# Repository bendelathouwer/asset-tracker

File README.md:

# LoRa asset tracker
a Lora asset tracker loosly based on a arduino mkr wan 1310. This asset tracker is going to be used on the quadVelo. 
And is made with the eurocircuits tool and for eurocircuits

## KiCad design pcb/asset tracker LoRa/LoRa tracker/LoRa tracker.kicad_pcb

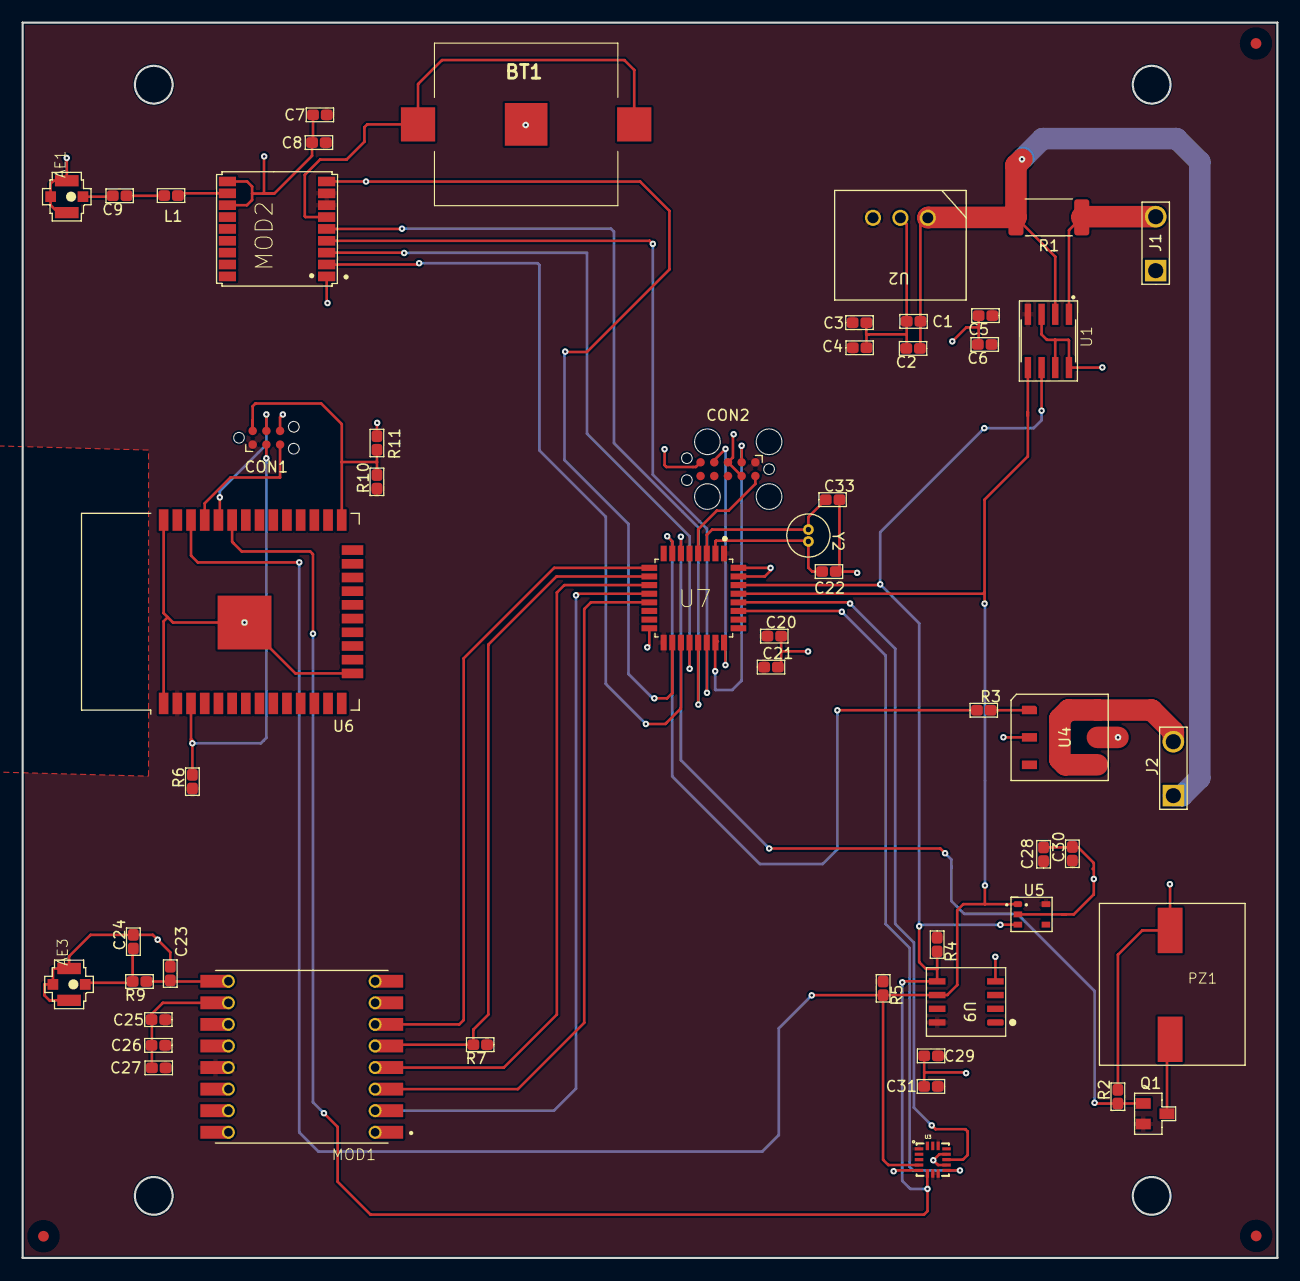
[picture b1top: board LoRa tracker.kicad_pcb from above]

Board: 2 copper layers, 116.3 x 114.5 mm, 53 parts (0 on the bottom side), 38 nets.

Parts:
AE1: sma; ufl connector
AE3: Antenna_Shield; ufl connector
BT1: Battery_Cell; 3012TR
C1, C3, C6, C8, C20, C28, C30: 100nF; 0603
C2, C4, C5, C7, C25, C29, C31: 10uF; 0603
C9: 120nF; 0603
C21, C26: 1uF; 0603
C22, C33: 6.8pF; 0603
C23, C24: NM; 0603
C27: 0.1uF; 0603
CON1: TAGconnect_ESP; Tag-Connect_TC2030-IDC-NL_2x03_P1.27mm_Vertical
CON2: jtag; Tag-Connect_TC2050-IDC-FP_2x05_P1.27mm_Vertical
J1, J2: Screw_Terminal_01x02; 2pin_screw
L1: 5n6; 0603
MOD1: RFM98W-433S2; XCVR_RFM98W-433S2
MOD2: teseo-LIV; SON_STM_TESEO-LIV3R
PZ1: buzzer; PROSIGNAL_ABI-017-RC
Q1: BSS138; sot-23,
R1: 100m Ohm; R_2512_6332Metric_Pad1.40x3.35mm_HandSolder
R2, R4, R5: 10K; 0603
R3: 220; 0603
R6, R7, R10: 10K; 0603RL
R9: 0; 0603RL
R11: NM; 0603RL
U1: INA219BxDCN; SOIC127P599X175-8N
U2: R-783.3-1.0; recom psu
U3: LIS3DH; QFN-16_0.5MM
U4: G3VM-61HR2(TR05); sop4 P=2.54
U5: DS28CM00R-A00+T; SOT-25
U6: ESP32-WROOM; ESP32-WROOM-32
U7: STM32L052K6Tx; QFP32P80_900X900X160L60X37N
U9: ATECC608B; soic p1.27 lengt 5.40
Y2: 32khz; crystal tht

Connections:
+3V3: C3.1, C4.1, C5.1, C6.1, C7.1, C8.1, C20.1, C21.1, C25.1, C26.1, C27.1, C28.1, C29.1, C30.1, C31.1, CON1.1 (VCC), CON2.1 (VCC), MOD1.13 (3.3V), MOD1.13_1 (3.3V), MOD2.7 (VCC_IO), MOD2.8 (VCC), Q1.2, R4.1, R5.1, R6.1, R7.1, R10.1, U1.4 (VS), U2.3 (OUT), U3.1 (VDD_IO), U3.7 (SDO/SA0), U3.8 (CS), U3.14 (VDD), U5.5 (VCC), U6.2 (3V3), U7.1 (VDD), U7.5 (VDDA), U7.17 (VDD), U9.8 (VCC)
/BUZZER: Q1.1, R2.1, U7.6 (PA0)
/CS: MOD1.5 (NSS), MOD1.5_1 (NSS), R7.2, U7.10 (PA4)
/INT1: U3.11 (INT1), U7.28 (PB5)
/INT2: U3.9 (INT2), U7.27 (PB4)
/LoRa_RFM/ANT: C23.1, MOD1.9 (ANT), MOD1.9_1 (ANT), R9.1
/MISO: MOD1.2 (MISO), MOD1.2_1 (MISO), U7.12 (PA6)
/MOSI: MOD1.3 (MOSI), MOD1.3_1 (MOSI), U7.13 (PA7)
/PPS: MOD2.4 (PPS), U7.22 (PA12)
/RESET: MOD1.6 (RESET), MOD1.6_1 (RESET), U7.9 (PA3)
/RESET_GPS: MOD2.9 (SYS_RESET), U7.18 (PA8)
/RX: MOD2.3 (RX), U7.20 (PA10)
/SCK: MOD1.4 (SCK), MOD1.4_1 (SCK), U7.11 (PA5)
/SCL: R5.2, U1.5 (SCL), U3.4 (SCL/SPC), U5.1 (SCL), U6.36 (IO22), U7.29 (PB6), U9.6 (SCL)
/SDA: R4.2, U1.6 (SDA), U3.6 (SDA/SDI/SDO), U5.3 (SDA), U6.33 (IO21), U7.30 (PB7), U9.5 (SDA)
/SSR: R3.1, U7.7 (PA1)
/TX: MOD2.2 (TX), U7.19 (PA9)
/WAKE: MOD2.5 (WAKE), U7.21 (PA11)
/esp32/GPIO0: CON1.2 (GPIO0), R10.2, R11.1, U6.25 (IO0)
/esp32/RESET: CON1.3 (RESET), R6.2, U6.3 (EN)
/esp32/RX: CON1.4 (RX), U6.34 (RXD0)
/esp32/TX: CON1.5 (TX), U6.35 (TXD0)
/mcu/OSC_32_IN: C22.1, U7.2 (PC14), Y2.2
/mcu/OSC_32_OUT: C33.1, U7.3 (PC15), Y2.1
/mcu/RST: CON2.10 (tRST), U7.4 (NRST)
/mcu/SWDCLK: CON2.4 (SWDCLK/TCK), U7.24 (PA14)
/mcu/SWDIO: CON2.2 (SWDIO/TMS), U7.23 (PA13)
GND: AE1.2 (Shield), AE3.2 (Shield), BT1.2 (-), C1.2, C2.2, C3.2, C4.2, C5.2, C6.2, C7.2, C8.2, C20.2, C21.2, C22.2, C23.2, C24.2, C25.2, C26.2, C27.2, C28.2, C29.2, C30.2, C31.2, C33.2, CON1.6 (GND), CON2.3 (GND), CON2.5 (GND), CON2.9 (GND), J1.1, MOD1.1 (GND), MOD1.1_1 (GND), MOD1.8 (GND), MOD1.8_1 (GND), MOD1.10 (GND), MOD1.10_1 (GND), MOD2.1 (GND), MOD2.10 (GND_RF), MOD2.12 (GND_RF), PZ1.2, R2.2, R11.2, U1.3 (GND), U1.7 (A0), U1.8 (A1), U2.2 (GND), U3.5 (GND), U3.10 (GND), U3.12 (GND), U4.2 (Catode), U4.5 (OUT2), U5.2 (GND), U6.1 (GND), U6.15 (GND), U6.38 (GND), U6.39 (GND-PAD), U7.16 (VSS), U7.31 (BOOT0), U7.32 (VSS), U9.4 (GND)
unnamed: AE1.1 (A), C9.2
unnamed: AE3.1 (A), C24.1, R9.2
unnamed: BT1.1 (+), MOD2.6 (VBAT)
unnamed: C9.1, L1.2
unnamed: J1.2, R1.1, U1.1 (IN+)
unnamed: J2.2, U4.4 (OUT1), U4.6 (OUT3)
unnamed: L1.1, MOD2.11 (RF_IN)
unnamed: PZ1.1, Q1.3
unnamed: R3.2, U4.1 (Anode)
VDC: C1.1, C2.1, J2.1, R1.2, U1.2 (IN-), U2.1 (IN)

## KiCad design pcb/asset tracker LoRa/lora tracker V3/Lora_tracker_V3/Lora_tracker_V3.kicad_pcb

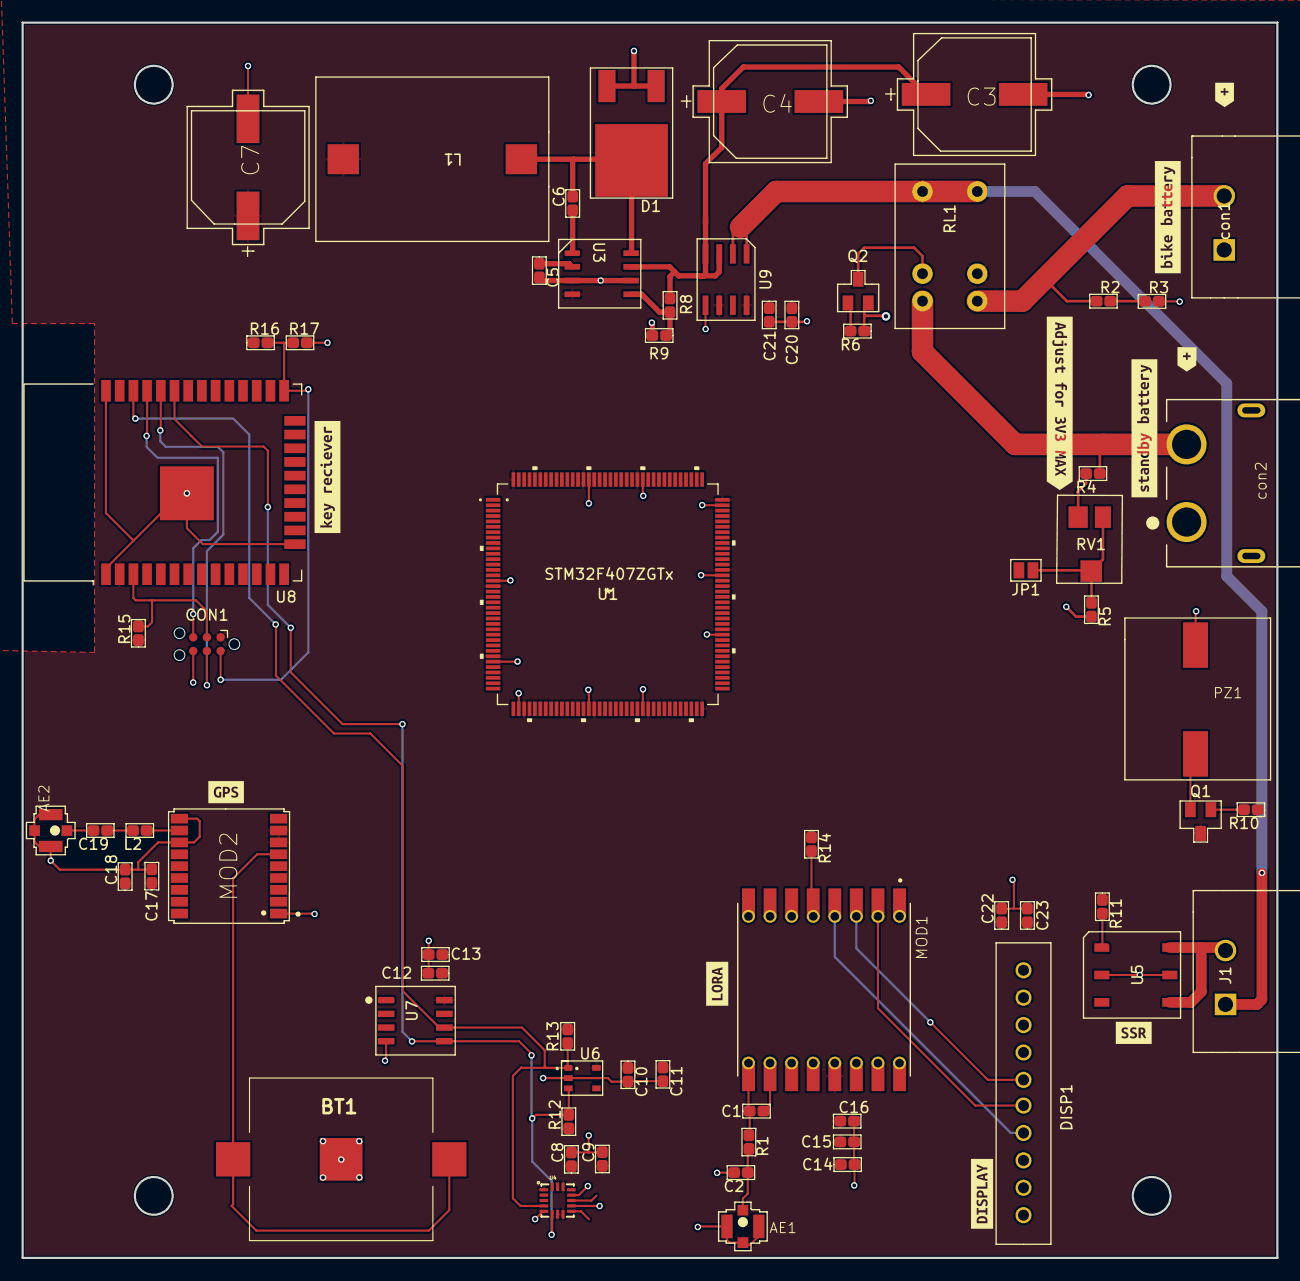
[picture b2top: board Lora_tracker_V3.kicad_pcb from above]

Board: 2 copper layers, 116.3 x 114.5 mm, 76 parts (0 on the bottom side), 36 nets.

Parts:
AE1: Antenna_Shield; ufl connector
AE2: sma; ufl connector
BT1: Battery_Cell; 3012TR
C1, C2: NM; 0603
C3: 68uF/100V; CAPAE1030X1050D1200L350X90N
C4: 0.22uF/100V; CAPAE1030X1050D1200L350X90N
C5, C6, C16: 0.1uF; 0603
C7: 68uF/10V; CAPAE1030X1050D1200L350X90N
C8, C11, C13, C14, C17, C20, C22: 10uF; 0603
C9, C10, C12, C18, C23: 100nF; 0603
C15: 1uF; 0603
C19: 120nF; 0603
C21: 10nF; 0603
CON1: TAGconnect_ESP; Tag-Connect_TC2030-IDC-NL_2x03_P1.27mm_Vertical
D1: MBRM5100; DPAK
DISP1: ConnectEVE; 10pin header
J1: Screw_Terminal_01x02; 2pin_screw
JP1: Jumper_2_Open; SolderJumper-2_P1.3mm_Open_Pad1.0x1.5mm
L1: 100uH; DO5022p
L2: 5n6; 0603
MOD1: RFM98W-433S2; XCVR_RFM98W-433S2
MOD2: teseo-LIV; SON_STM_TESEO-LIV3R
PZ1: buzzer; PROSIGNAL_ABI-017-RC
Q1, Q2: BSS138; sot-23,
R1: 0; 0603RL
R2: 1Mohm; 0603
R3: 58Kohm; 0603
R4: 900K; 0603
R5: 58K; 0603
R6, R10, R12, R13: 10K; 0603
R8: 43.5Kohm/1%; 0603
R9: 130Kohm/1%; 0603
R11: 220; 0603
R14, R15, R16: 10K; 0603RL
R17: NM; 0603RL
RL1: Relais; G5V-1
RV1: 100K; 3314G-1-201E bourns trimmer
U1: STM32F407ZGTx; STM32F407ZGT6
U3: MAX5035AUSA; soic HV clearance
U4: LIS3DH; QFN-16_0.5MM
U5: G3VM-61HR2(TR05); sop4 P=2.54
U6: DS28CM00R-A00+T; SOT-25
U7: ATECC608B; soic p1.27 lengt 5.40
U8: ESP32-WROOM; ESP32-WROOM-32
U9: MLX91221; SOIC-8
con1: screw terminal; 2pin_screw
con2: xt60; AMASS_XT60PW-F
kibuzzard-613B3452: G***; kibuzzard-613B3452
kibuzzard-613B3465: G***; kibuzzard-613B3465
kibuzzard-613B6735: G***; kibuzzard-613B6735
kibuzzard-613B6746: G***; kibuzzard-613B6746
kibuzzard-613B6752: G***; kibuzzard-613B6752
kibuzzard-613F18F5: G***; kibuzzard-613F18F5
kibuzzard-613F1907: G***; kibuzzard-613F1907
kibuzzard-61389C09, kibuzzard-61389C09#2: G***; kibuzzard-61389C09
kibuzzard-61389CC5: G***; kibuzzard-61389CC5

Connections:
+3V3: C7.1, C8.1, C9.1, C10.1, C11.1, C12.1, C13.1, C14.1, C15.1, C16.1, C17.1, C18.1, C20.1, C21.1, C22.1, C23.1, CON1.1 (VCC), DISP1.9 (VCC_3V3), L1.2, MOD1.13 (3.3V), MOD1.13_1 (3.3V), MOD2.7 (VCC_IO), MOD2.8 (VCC), Q1.3 (D), R10.1, R12.1, R13.1, R14.1, R15.1, R16.1, RL1.2, U1.17 (VDD), U1.30 (VDD), U1.33 (VDDA), U1.39 (VDD), U1.52 (VDD), U1.62 (VDD), U1.72 (VDD), U1.84 (VDD), U1.95 (VDD), U1.108 (VDD), U1.121 (VDD), U1.131 (VDD), U1.144 (VDD), U3.4 (FB), U4.1 (VDD_IO), U4.7 (SDO/SA0), U4.8 (CS), U4.14 (VDD), U6.5 (VCC), U7.8 (VCC), U8.2 (3V3), U9.6 (VREF), U9.8 (VDD)
/BUZZER: Q1.1 (G), R10.2
/CLK: DISP1.4 (SCK), MOD1.4 (SCK), MOD1.4_1 (SCK)
/CS: MOD1.5 (NSS), MOD1.5_1 (NSS), R14.2
/Lora_RFM/ANT: C1.1, MOD1.9 (ANT), MOD1.9_1 (ANT), R1.1
/MISO: DISP1.5 (MISO), MOD1.2 (MISO), MOD1.2_1 (MISO)
/MOSI: DISP1.6 (MOSI), MOD1.3 (MOSI), MOD1.3_1 (MOSI)
/RELAY: Q2.1 (G), R6.2
/RESET_LORA: MOD1.6 (RESET), MOD1.6_1 (RESET)
/SCL: R13.2, U4.4 (SCL/SPC), U6.1 (SCL), U7.6 (SCL), U8.36 (IO22)
/SDA: R12.2, U4.6 (SDA/SDI/SDO), U6.3 (SDA), U7.5 (SDA), U8.33 (IO21)
/Voltage1: R2.2, R3.1
/esp32/GPIO0: CON1.2 (GPIO0), R16.2, R17.1, U8.25 (IO0)
/esp32/RESET: CON1.3 (RESET), R15.2, U8.3 (EN)
/esp32/RX: CON1.4 (RX), U8.34 (RXD0)
/esp32/TX: CON1.5 (TX), U8.35 (TXD0)
/voeding/DC_DC/VIN DC_DC: C3.1, C4.1, R8.1, U3.7 (VIN), U9.3 (IP-), U9.4 (IP-)
GND: AE1.2 (Shield), AE2.2 (Shield), BT1.2 (-), C1.2, C2.2, C3.2, C4.2, C5.2, C7.2, C8.2, C9.2, C10.2, C11.2, C12.2, C13.2, C14.2, C15.2, C16.2, C17.2, C18.2, C20.2, C21.2, C22.2, C23.2, CON1.6 (GND), D1.1, D1.3, DISP1.10 (GND), MOD1.1 (GND), MOD1.1_1 (GND), MOD1.8 (GND), MOD1.8_1 (GND), MOD1.10 (GND), MOD1.10_1 (GND), MOD2.1 (GND), MOD2.10 (GND_RF), MOD2.12 (GND_RF), PZ1.2, Q2.2 (S), R3.2, R5.2, R6.1, R9.2, R17.2, U1.16 (VSS), U1.31 (VSSA), U1.38 (VSS), U1.51 (VSS), U1.61 (VSS), U1.83 (VSS), U1.94 (VSS), U1.107 (VSS), U1.120 (VSS), U1.130 (VSS), U3.3 (SGND), U3.6 (GND), U4.5 (GND), U4.10 (GND), U4.12 (GND), U5.2 (Catode), U5.5 (OUT2), U6.2 (GND), U7.4 (GND), U8.1 (GND), U8.15 (GND), U8.38 (GND), U8.39 (GND-PAD), U9.5 (GND), con1.1 (-), con2.1 (-)
unnamed: AE1.1 (A), C2.1, R1.2
unnamed: AE2.1 (A), C19.2
unnamed: BT1.1 (+), MOD2.6 (VBAT)
unnamed: C5.1, U3.2 (VD)
unnamed: C6.1, U3.1 (BST)
unnamed: C6.2, D1.4, L1.1, U3.8 (LX)
unnamed: C19.1, L2.2
unnamed: J1.2, U5.4 (OUT1), U5.6 (OUT3)
unnamed: JP1.1 (A), R5.1, RV1.2, RV1.3
unnamed: L2.1, MOD2.11 (RF_IN)
unnamed: PZ1.1, Q1.2 (S)
unnamed: Q2.3 (D), RL1.1
unnamed: R2.1, RL1.5, con1.2 (+)
unnamed: R4.1, RL1.4, con2.2 (+)
unnamed: R4.2, RV1.1
unnamed: R8.2, R9.1, U3.5 (ON/~OFF)
unnamed: R11.2, U5.1 (Anode)
VDC: J1.1, RL1.3, U9.1 (IP+), U9.2 (IP+)

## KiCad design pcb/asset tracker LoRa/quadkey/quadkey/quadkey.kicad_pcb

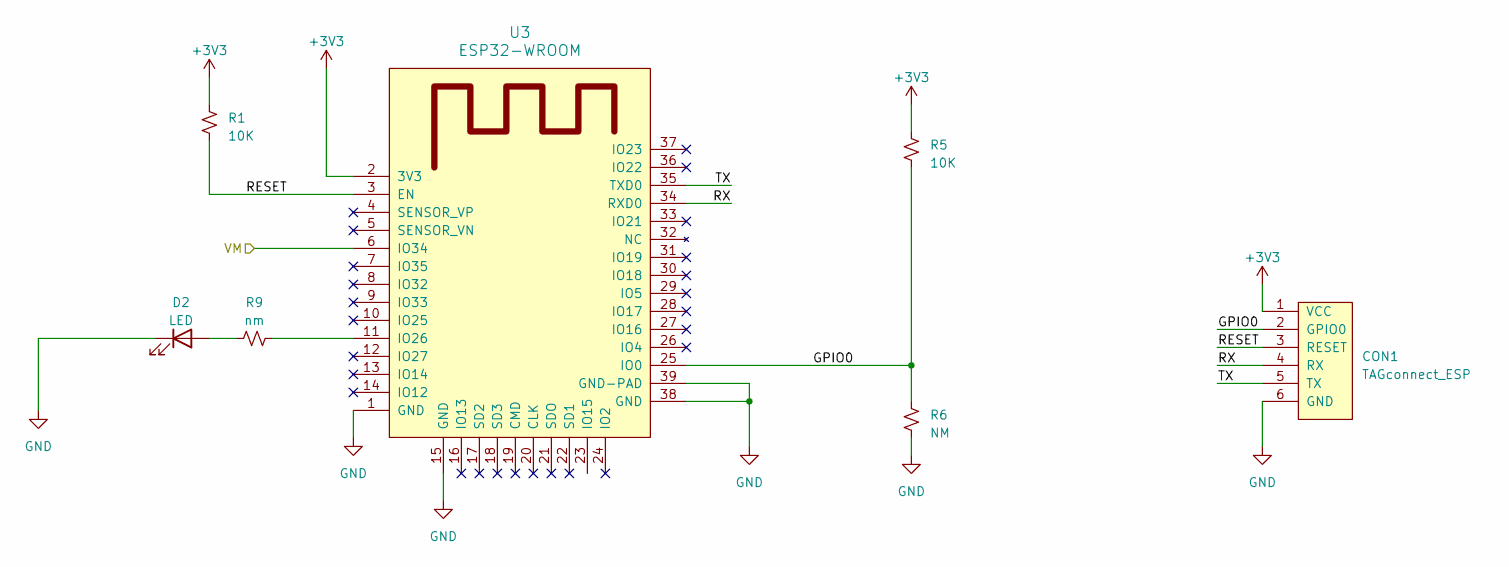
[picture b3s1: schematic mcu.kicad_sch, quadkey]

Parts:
CON1: TAGconnect_ESP; Tag-Connect_TC2030-IDC-NL_2x03_P1.27mm_Vertical
D2: LED; led0603
R1, R5: 10K; 0603RL
R6: NM; 0603RL
R9: nm; 0603RL
U3: ESP32-WROOM; ESP32-WROOM-32

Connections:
+3V3: CON1.1 (VCC), R1.1, R5.1, U3.2 (3V3); also elsewhere on the board
/mcu/GPIO0: CON1.2 (GPIO0), R5.2, R6.1, U3.25 (IO0)
/mcu/RESET: CON1.3 (RESET), R1.2, U3.3 (EN)
/mcu/RX: CON1.4 (RX), U3.34 (RXD0)
/mcu/TX: CON1.5 (TX), U3.35 (TXD0)
/mcu/VM: U3.6 (IO34); also elsewhere on the board
GND: CON1.6 (GND), D2.1 (K), R6.2, U3.1 (GND), U3.15 (GND), U3.38 (GND), U3.39 (GND-PAD); also elsewhere on the board
unnamed: D2.2 (A), R9.1
unnamed: R9.2, U3.11 (IO26)

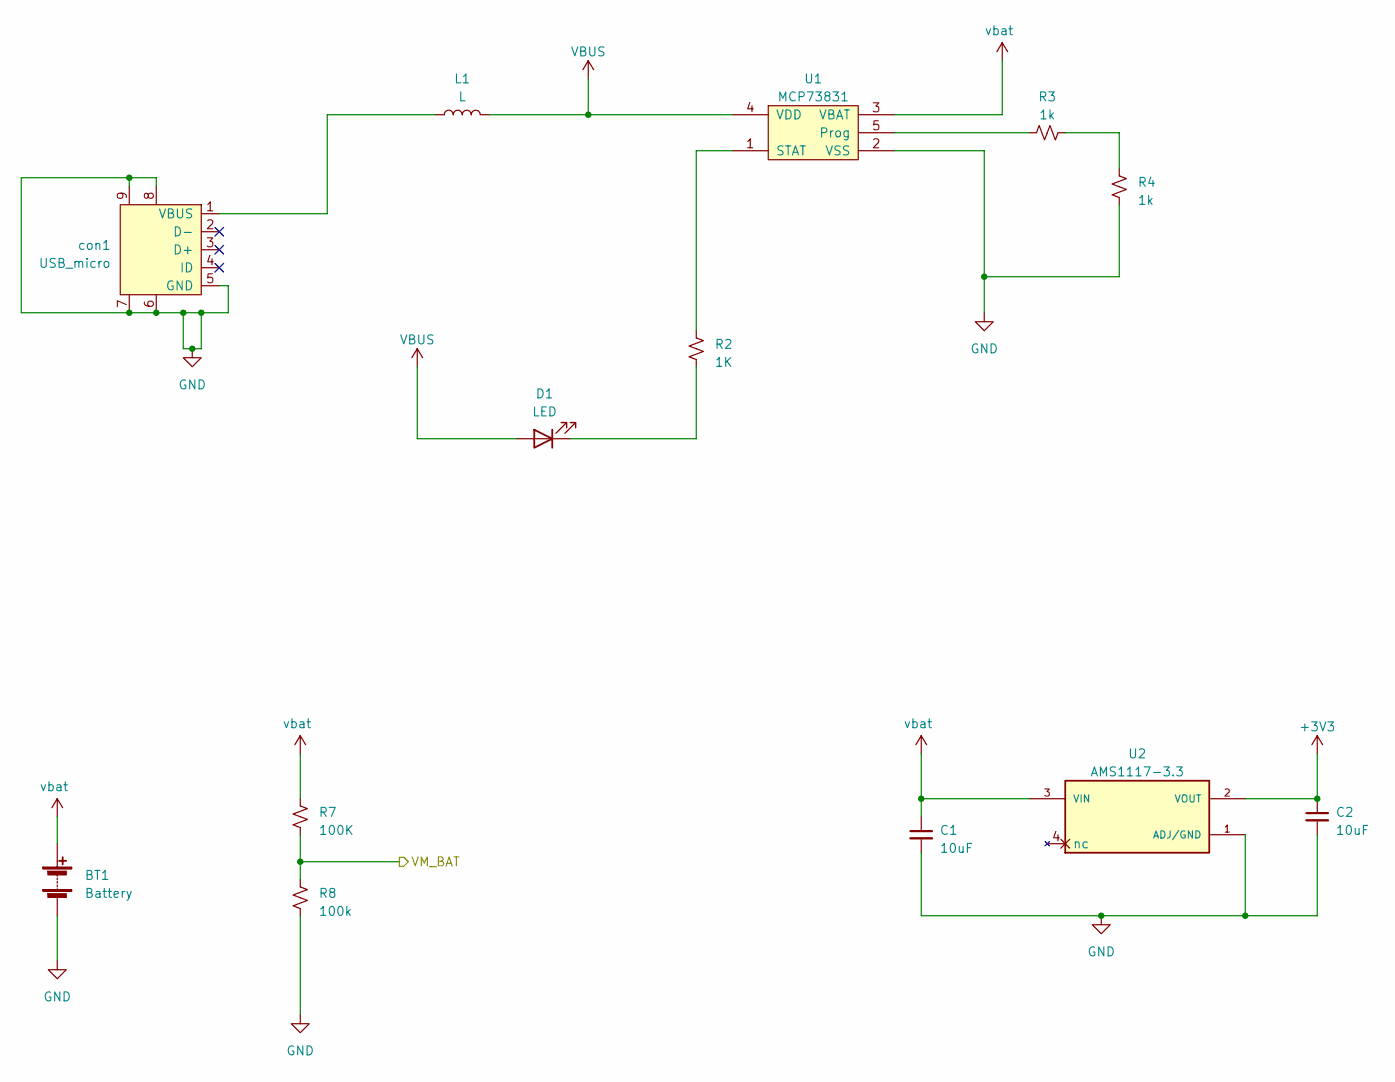
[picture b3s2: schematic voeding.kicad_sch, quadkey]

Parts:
BT1: Battery; jst 2 pin
C1, C2: 10uF; 0603
D1: LED; led0603
L1: L; 0603RL
R2: 1K; 0603RL
R3, R4: 1k; 0603RL
R7: 100K; 0603RL
R8: 100k; 0603RL
U1: MCP73831; SOT-25
U2: AMS1117-3.3; SOT229P700X180-4N; PARTREV NA
con1: USB_micro; MILLMAX_897-43-005-00-100001

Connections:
+3V3: C2.1, U2.2 (VOUT); also elsewhere on the board
/mcu/VM: R7.1, R8.2; also elsewhere on the board
GND: BT1.2 (-), C1.2, C2.2, R4.1, R8.1, U1.2 (VSS), U2.1 (ADJ/GND), con1.5 (GND), con1.6, con1.7, con1.8, con1.9; also elsewhere on the board
unnamed: D1.1 (K), R2.2
unnamed: L1.1, con1.1 (VBUS)
unnamed: R2.1, U1.1 (STAT)
unnamed: R3.1, U1.5 (Prog)
unnamed: R3.2, R4.2
VBAT: BT1.1 (+), C1.1, R7.2, U1.3 (VBAT), U2.3 (VIN)
VBUS: D1.2 (A), L1.2, U1.4 (VDD)

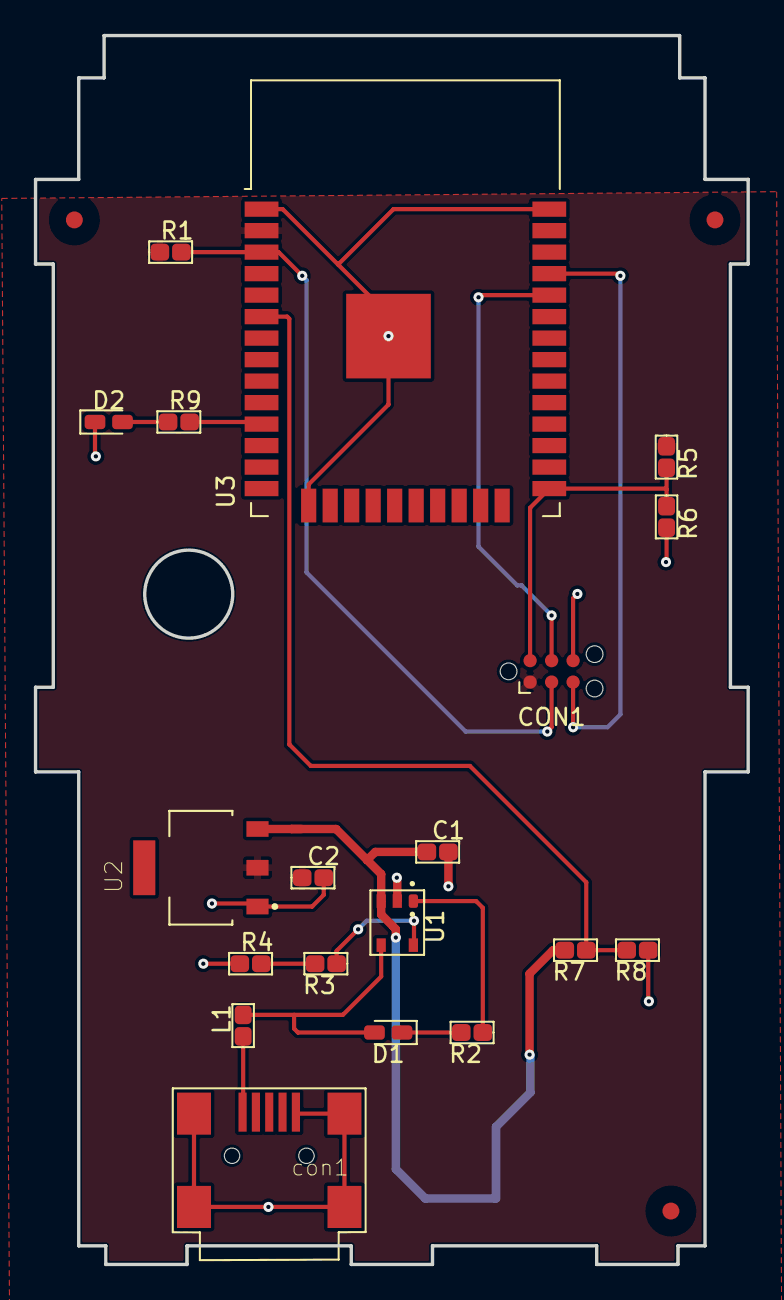
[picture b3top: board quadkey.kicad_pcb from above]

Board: 2 copper layers, 42.1 x 72.6 mm, 20 parts (1 on the bottom side), 16 nets.

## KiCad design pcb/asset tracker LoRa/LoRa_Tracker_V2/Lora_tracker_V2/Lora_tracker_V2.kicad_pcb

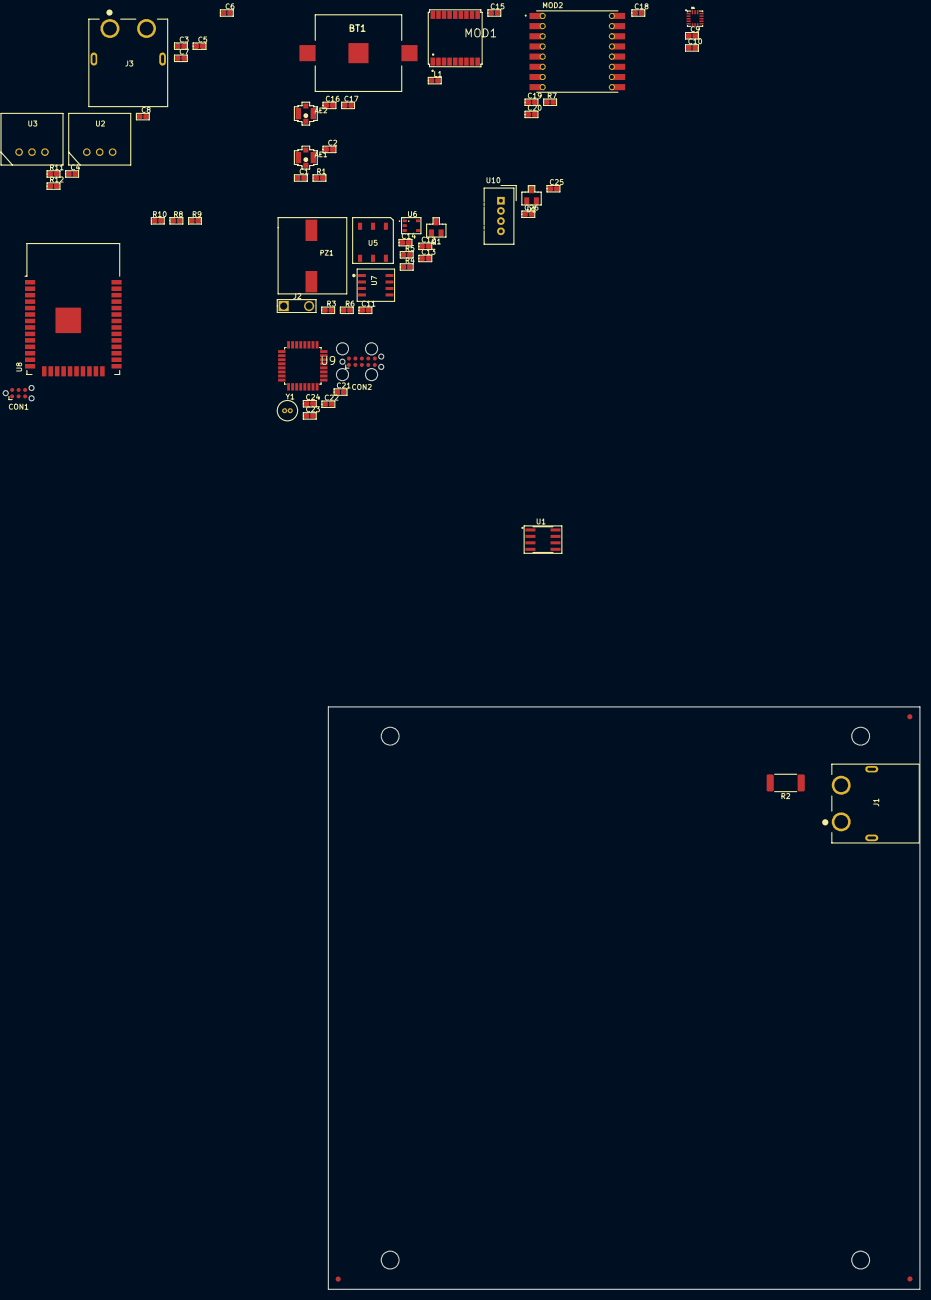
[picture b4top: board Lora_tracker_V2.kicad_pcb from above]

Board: 2 copper layers, 116.3 x 114.5 mm, 63 parts (0 on the bottom side), 44 nets, no tracks yet.

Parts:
AE1: Antenna_Shield; ufl connector
AE2: sma; ufl connector
BT1: Battery_Cell; 3012TR
C1, C2: NM; 0603
C3, C5, C7, C10, C11, C13, C16, C21, C25: 100nF; 0603
C4, C6, C8, C9, C12, C14, C15, C18, C26: 10uF; 0603
C17: 120nF; 0603
C19, C22: 1uF; 0603
C20: 0.1uF; 0603
C23, C24: 6.8pF; 0603
CON1: TAGconnect_ESP; Tag-Connect_TC2030-IDC-NL_2x03_P1.27mm_Vertical
CON2: jtag; Tag-Connect_TC2050-IDC-FP_2x05_P1.27mm_Vertical
D1: PESD15VL2BT; sot-23,
J1, J3: Screw_Terminal_01x02; AMASS_XT60PW-F
J2: Screw_Terminal_01x02; 2pin_screw
L1: 5n6; 0603
MOD1: teseo-LIV; SON_STM_TESEO-LIV3R
MOD2: RFM98W-433S2; XCVR_RFM98W-433S2
PZ1: buzzer; PROSIGNAL_ABI-017-RC
Q1: BSS138; sot-23,
R1: 0; 0603RL
R2: 100m Ohm; R_2512_6332Metric_Pad1.40x3.35mm_HandSolder
R3, R5, R6: 10K; 0603
R4: 220; 0603
R7, R8, R9: 10K; 0603RL
R10: NM; 0603RL
R11: 1M ohm; 0603
R12: 36Kohm; 0603
U1: INA219BxDCN; SOIC127P599X175-8N
U2, U3: recom_psu; recom psu
U4: LIS3DH; QFN-16_0.5MM
U5: G3VM-61HR2(TR05); sop4 P=2.54
U6: DS28CM00R-A00+T; SOT-25
U7: ATECC608B; soic p1.27 lengt 5.40
U8: ESP32-WROOM; ESP32-WROOM-32
U9: STM32L052K6Tx; QFP32P80_900X900X160L60X37N
U10: nextion; NS-Tech_Grove_1x04_P2mm_Vertical
Y1: 32khz; crystal tht

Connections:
+3V3: C5.1, C6.1, C9.1, C10.1, C11.1, C12.1, C13.1, C14.1, C15.1, C16.1, C18.1, C19.1, C20.1, C21.1, C22.1, CON1.1 (VCC), CON2.1 (VCC), MOD1.7 (VCC_IO), MOD1.8 (VCC), MOD2.13 (3.3V), MOD2.13_1 (3.3V), Q1.2, R5.1, R6.1, R7.1, R8.1, R9.1, U1.4 (VS), U2.3 (Vout), U4.1 (VDD_IO), U4.7 (SDO/SA0), U4.8 (CS), U4.14 (VDD), U6.5 (VCC), U7.8 (VCC), U8.2 (3V3), U9.1 (VDD), U9.5 (VDDA), U9.17 (VDD)
+5V: C7.1, C8.1, C25.1, C26.1, U3.3 (Vout), U10.1 (5V)
/BUZZER: Q1.1, R3.1, U9.6 (PA0)
/CS: MOD2.5 (NSS), MOD2.5_1 (NSS), R7.2, U9.10 (PA4)
/INT1: U4.11 (INT1), U9.28 (PB5)
/INT2: U4.9 (INT2), U9.27 (PB4)
/LoRa_RFM/ANT: C1.1, MOD2.9 (ANT), MOD2.9_1 (ANT), R1.1
/MISO: MOD2.2 (MISO), MOD2.2_1 (MISO), U9.12 (PA6)
/MOSI: MOD2.3 (MOSI), MOD2.3_1 (MOSI), U9.13 (PA7)
/PPS: MOD1.4 (PPS), U9.22 (PA12)
/RESET: MOD2.6 (RESET), MOD2.6_1 (RESET), U9.26 (PB3)
/RESET_GPS: MOD1.9 (SYS_RESET), U9.18 (PA8)
/RX_DIPSLAY: D1.1 (C1), D1.2 (C2), U9.9 (PA3), U10.2 (TX)
/RX_GPS: MOD1.3 (RX), U9.20 (PA10)
/SCK: MOD2.4 (SCK), MOD2.4_1 (SCK), U9.11 (PA5)
/SCL: R6.2, U1.5 (SCL), U4.4 (SCL/SPC), U6.1 (SCL), U7.6 (SCL), U8.36 (IO22), U9.29 (PB6)
/SDA: R5.2, U1.6 (SDA), U4.6 (SDA/SDI/SDO), U6.3 (SDA), U7.5 (SDA), U8.33 (IO21), U9.30 (PB7)
/SSR: R4.1, U9.7 (PA1)
/TX_DIPSLAY: U9.8 (PA2), U10.3 (RX)
/TX_GPS: MOD1.2 (TX), U9.19 (PA9)
/WAKE: MOD1.5 (WAKE), U9.21 (PA11)
/esp32/GPIO0: CON1.2 (GPIO0), R9.2, R10.1, U8.25 (IO0)
/esp32/RESET: CON1.3 (RESET), R8.2, U8.3 (EN)
/esp32/RX: CON1.4 (RX), U8.34 (RXD0)
/esp32/TX: CON1.5 (TX), U8.35 (TXD0)
/mcu/OSC_32_IN: C23.1, U9.2 (PC14), Y1.2
/mcu/OSC_32_OUT: C24.1, U9.3 (PC15), Y1.1
/mcu/RST: CON2.10 (tRST), U9.4 (NRST)
/mcu/SWDCLK: CON2.4 (SWDCLK/TCK), U9.24 (PA14)
/mcu/SWDIO: CON2.2 (SWDIO/TMS), U9.23 (PA13)
/voeding/HV_MESS: R11.2, R12.1
GND: AE1.2 (Shield), AE2.2 (Shield), BT1.2 (-), C1.2, C2.2, C3.2, C4.2, C5.2, C6.2, C7.2, C8.2, C9.2, C10.2, C11.2, C12.2, C13.2, C14.2, C15.2, C16.2, C18.2, C19.2, C20.2, C21.2, C22.2, C23.2, C24.2, C25.2, C26.2, CON1.6 (GND), CON2.3 (GND), CON2.5 (GND), CON2.9 (GND), D1.3 (C3), J1.1, MOD1.1 (GND), MOD1.10 (GND_RF), MOD1.12 (GND_RF), MOD2.1 (GND), MOD2.1_1 (GND), MOD2.8 (GND), MOD2.8_1 (GND), MOD2.10 (GND), MOD2.10_1 (GND), PZ1.2, R3.2, R10.2, U1.3 (GND), U1.7 (A0), U1.8 (A1), U2.2 (GND), U3.2 (GND), U4.5 (GND), U4.10 (GND), U4.12 (GND), U5.2 (Catode), U5.5 (OUT2), U6.2 (GND), U7.4 (GND), U8.1 (GND), U8.15 (GND), U8.38 (GND), U8.39 (GND-PAD), U9.16 (VSS), U9.31 (BOOT0), U9.32 (VSS), U10.4 (GND)
unnamed: AE1.1 (A), C2.1, R1.2
unnamed: AE2.1 (A), C17.2
unnamed: BT1.1 (+), MOD1.6 (VBAT)
unnamed: C17.1, L1.2
unnamed: J1.2, R2.1, U1.1 (IN+)
unnamed: J2.2, U5.4 (OUT1), U5.6 (OUT3)
unnamed: J3.1, R12.2
unnamed: J3.2, R11.1
unnamed: L1.1, MOD1.11 (RF_IN)
unnamed: PZ1.1, Q1.3
unnamed: R4.2, U5.1 (Anode)
VDC: C3.1, C4.1, J2.1, R2.2, U1.2 (IN-), U2.1 (Vin), U3.1 (Vin)

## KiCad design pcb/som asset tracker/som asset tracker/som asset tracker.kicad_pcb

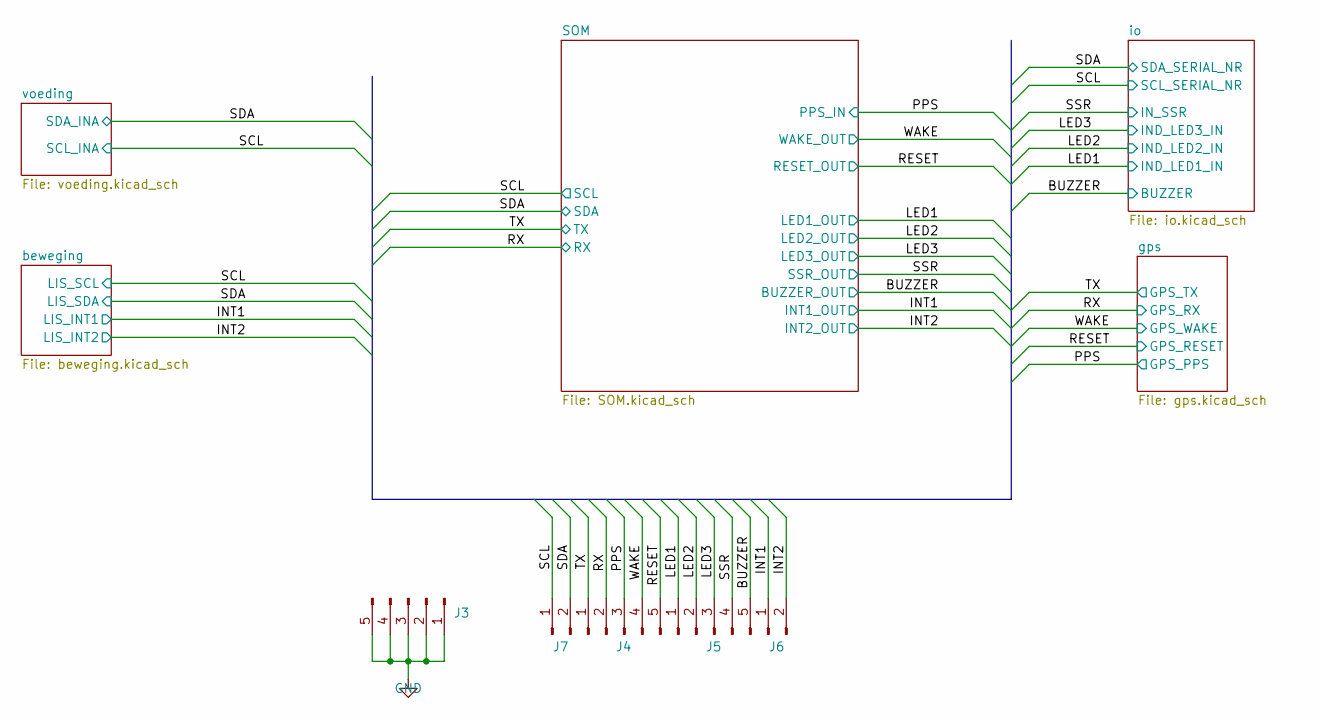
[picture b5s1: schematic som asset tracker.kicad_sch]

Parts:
J3, J4, J5: Conn_01x05_Male; 5pin header
J6, J7: Conn_01x02_Male; 2 pin header

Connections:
/BUZZER: J5.5; also elsewhere on the board
/INT1: J6.1; also elsewhere on the board
/INT2: J6.2; also elsewhere on the board
/LED1: J5.1; also elsewhere on the board
/LED2: J5.2; also elsewhere on the board
/LED3: J5.3; also elsewhere on the board
/PPS: J4.3; also elsewhere on the board
/RESET: J4.5; also elsewhere on the board
/RX: J4.2; also elsewhere on the board
/SCL: J7.1; also elsewhere on the board
/SDA: J7.2; also elsewhere on the board
/SSR: J5.4; also elsewhere on the board
/TX: J4.1; also elsewhere on the board
/WAKE: J4.4; also elsewhere on the board
GND: J3.1, J3.2, J3.3, J3.4, J3.5; also elsewhere on the board

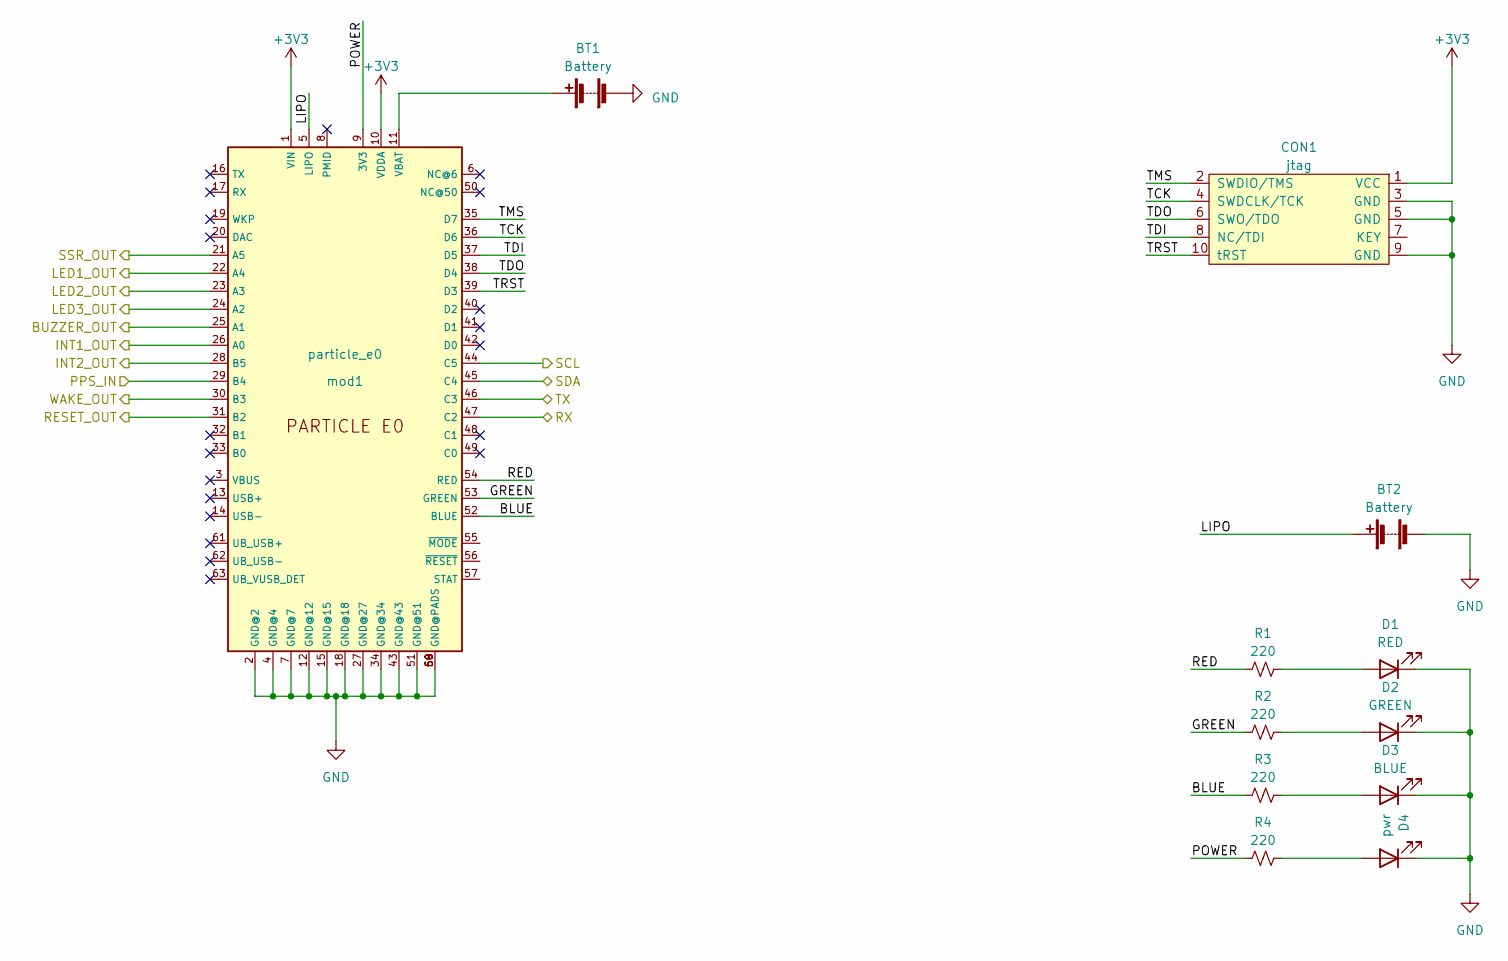
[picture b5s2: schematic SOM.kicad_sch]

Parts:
BT1: Battery; 3012TR
BT2: Battery; jst 2 pin
CON1: jtag; SAMTEC_FTSH-105-01-F-DV-P-TR
D1: RED; led0603
D2: GREEN; led0603
D3: BLUE; led0603
D4: pwr; led0603
R1, R2, R3, R4: 220; 0603RL
mod1: particle_e0; E0

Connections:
+3V3: CON1.1 (VCC), mod1.1 (VIN), mod1.10 (VDDA); also elsewhere on the board
/BUZZER: mod1.25 (A1); also elsewhere on the board
/INT1: mod1.26 (A0); also elsewhere on the board
/INT2: mod1.28 (B5); also elsewhere on the board
/LED1: mod1.22 (A4); also elsewhere on the board
/LED2: mod1.23 (A3); also elsewhere on the board
/LED3: mod1.24 (A2); also elsewhere on the board
/PPS: mod1.29 (B4); also elsewhere on the board
/RESET: mod1.31 (B2); also elsewhere on the board
/RX: mod1.47 (C2); also elsewhere on the board
/SCL: mod1.44 (C5); also elsewhere on the board
/SDA: mod1.45 (C4); also elsewhere on the board
/SOM/BLUE: R3.1, mod1.52 (BLUE)
/SOM/GREEN: R2.1, mod1.53 (GREEN)
/SOM/LIPO: BT2.1 (+), mod1.5 (LIPO)
/SOM/POWER: R4.1, mod1.9 (3V3)
/SOM/RED: R1.1, mod1.54 (RED)
/SOM/TCK: CON1.4 (SWDCLK/TCK), mod1.36 (D6)
/SOM/TDI: CON1.8 (NC/TDI), mod1.37 (D5)
/SOM/TDO: CON1.6 (SWO/TDO), mod1.38 (D4)
/SOM/TMS: CON1.2 (SWDIO/TMS), mod1.35 (D7)
/SOM/TRST: CON1.10 (tRST), mod1.39 (D3)
/SSR: mod1.21 (A5); also elsewhere on the board
/TX: mod1.46 (C3); also elsewhere on the board
/WAKE: mod1.30 (B3); also elsewhere on the board
GND: BT1.2 (-), BT2.2 (-), CON1.3 (GND), CON1.5 (GND), CON1.9 (GND), D1.1 (K), D2.1 (K), D3.1 (K), D4.1 (K), mod1.2 (GND@2), mod1.4 (GND@4), mod1.7 (GND@7), mod1.12 (GND@12), mod1.15 (GND@15), mod1.18 (GND@18), mod1.27 (GND@27), mod1.34 (GND@34), mod1.43 (GND@43), mod1.51 (GND@51), mod1.58 (GND@PADS), mod1.59 (GND@PADS), mod1.60 (GND@PADS); also elsewhere on the board
unnamed: BT1.1 (+), mod1.11 (VBAT)
unnamed: D1.2 (A), R1.2
unnamed: D2.2 (A), R2.2
unnamed: D3.2 (A), R3.2
unnamed: D4.2 (A), R4.2

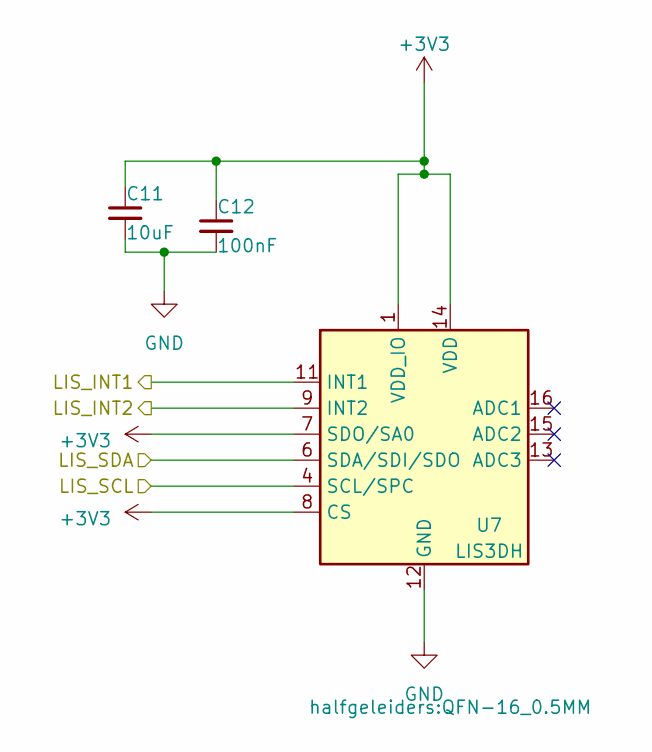
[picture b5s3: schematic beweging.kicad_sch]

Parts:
C11: 10uF; 0603
C12: 100nF; 0603
U7: LIS3DH; QFN-16_0.5MM

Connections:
+3V3: C11.1, C12.1, U7.1 (VDD_IO), U7.7 (SDO/SA0), U7.8 (CS), U7.14 (VDD); also elsewhere on the board
/INT1: U7.11 (INT1); also elsewhere on the board
/INT2: U7.9 (INT2); also elsewhere on the board
/SCL: U7.4 (SCL/SPC); also elsewhere on the board
/SDA: U7.6 (SDA/SDI/SDO); also elsewhere on the board
GND: C11.2, C12.2, U7.5 (GND), U7.10 (GND), U7.12 (GND); also elsewhere on the board

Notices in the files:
parts and their libraries:
Copyright 2021 Accelerated Designs. All rights reserved.
